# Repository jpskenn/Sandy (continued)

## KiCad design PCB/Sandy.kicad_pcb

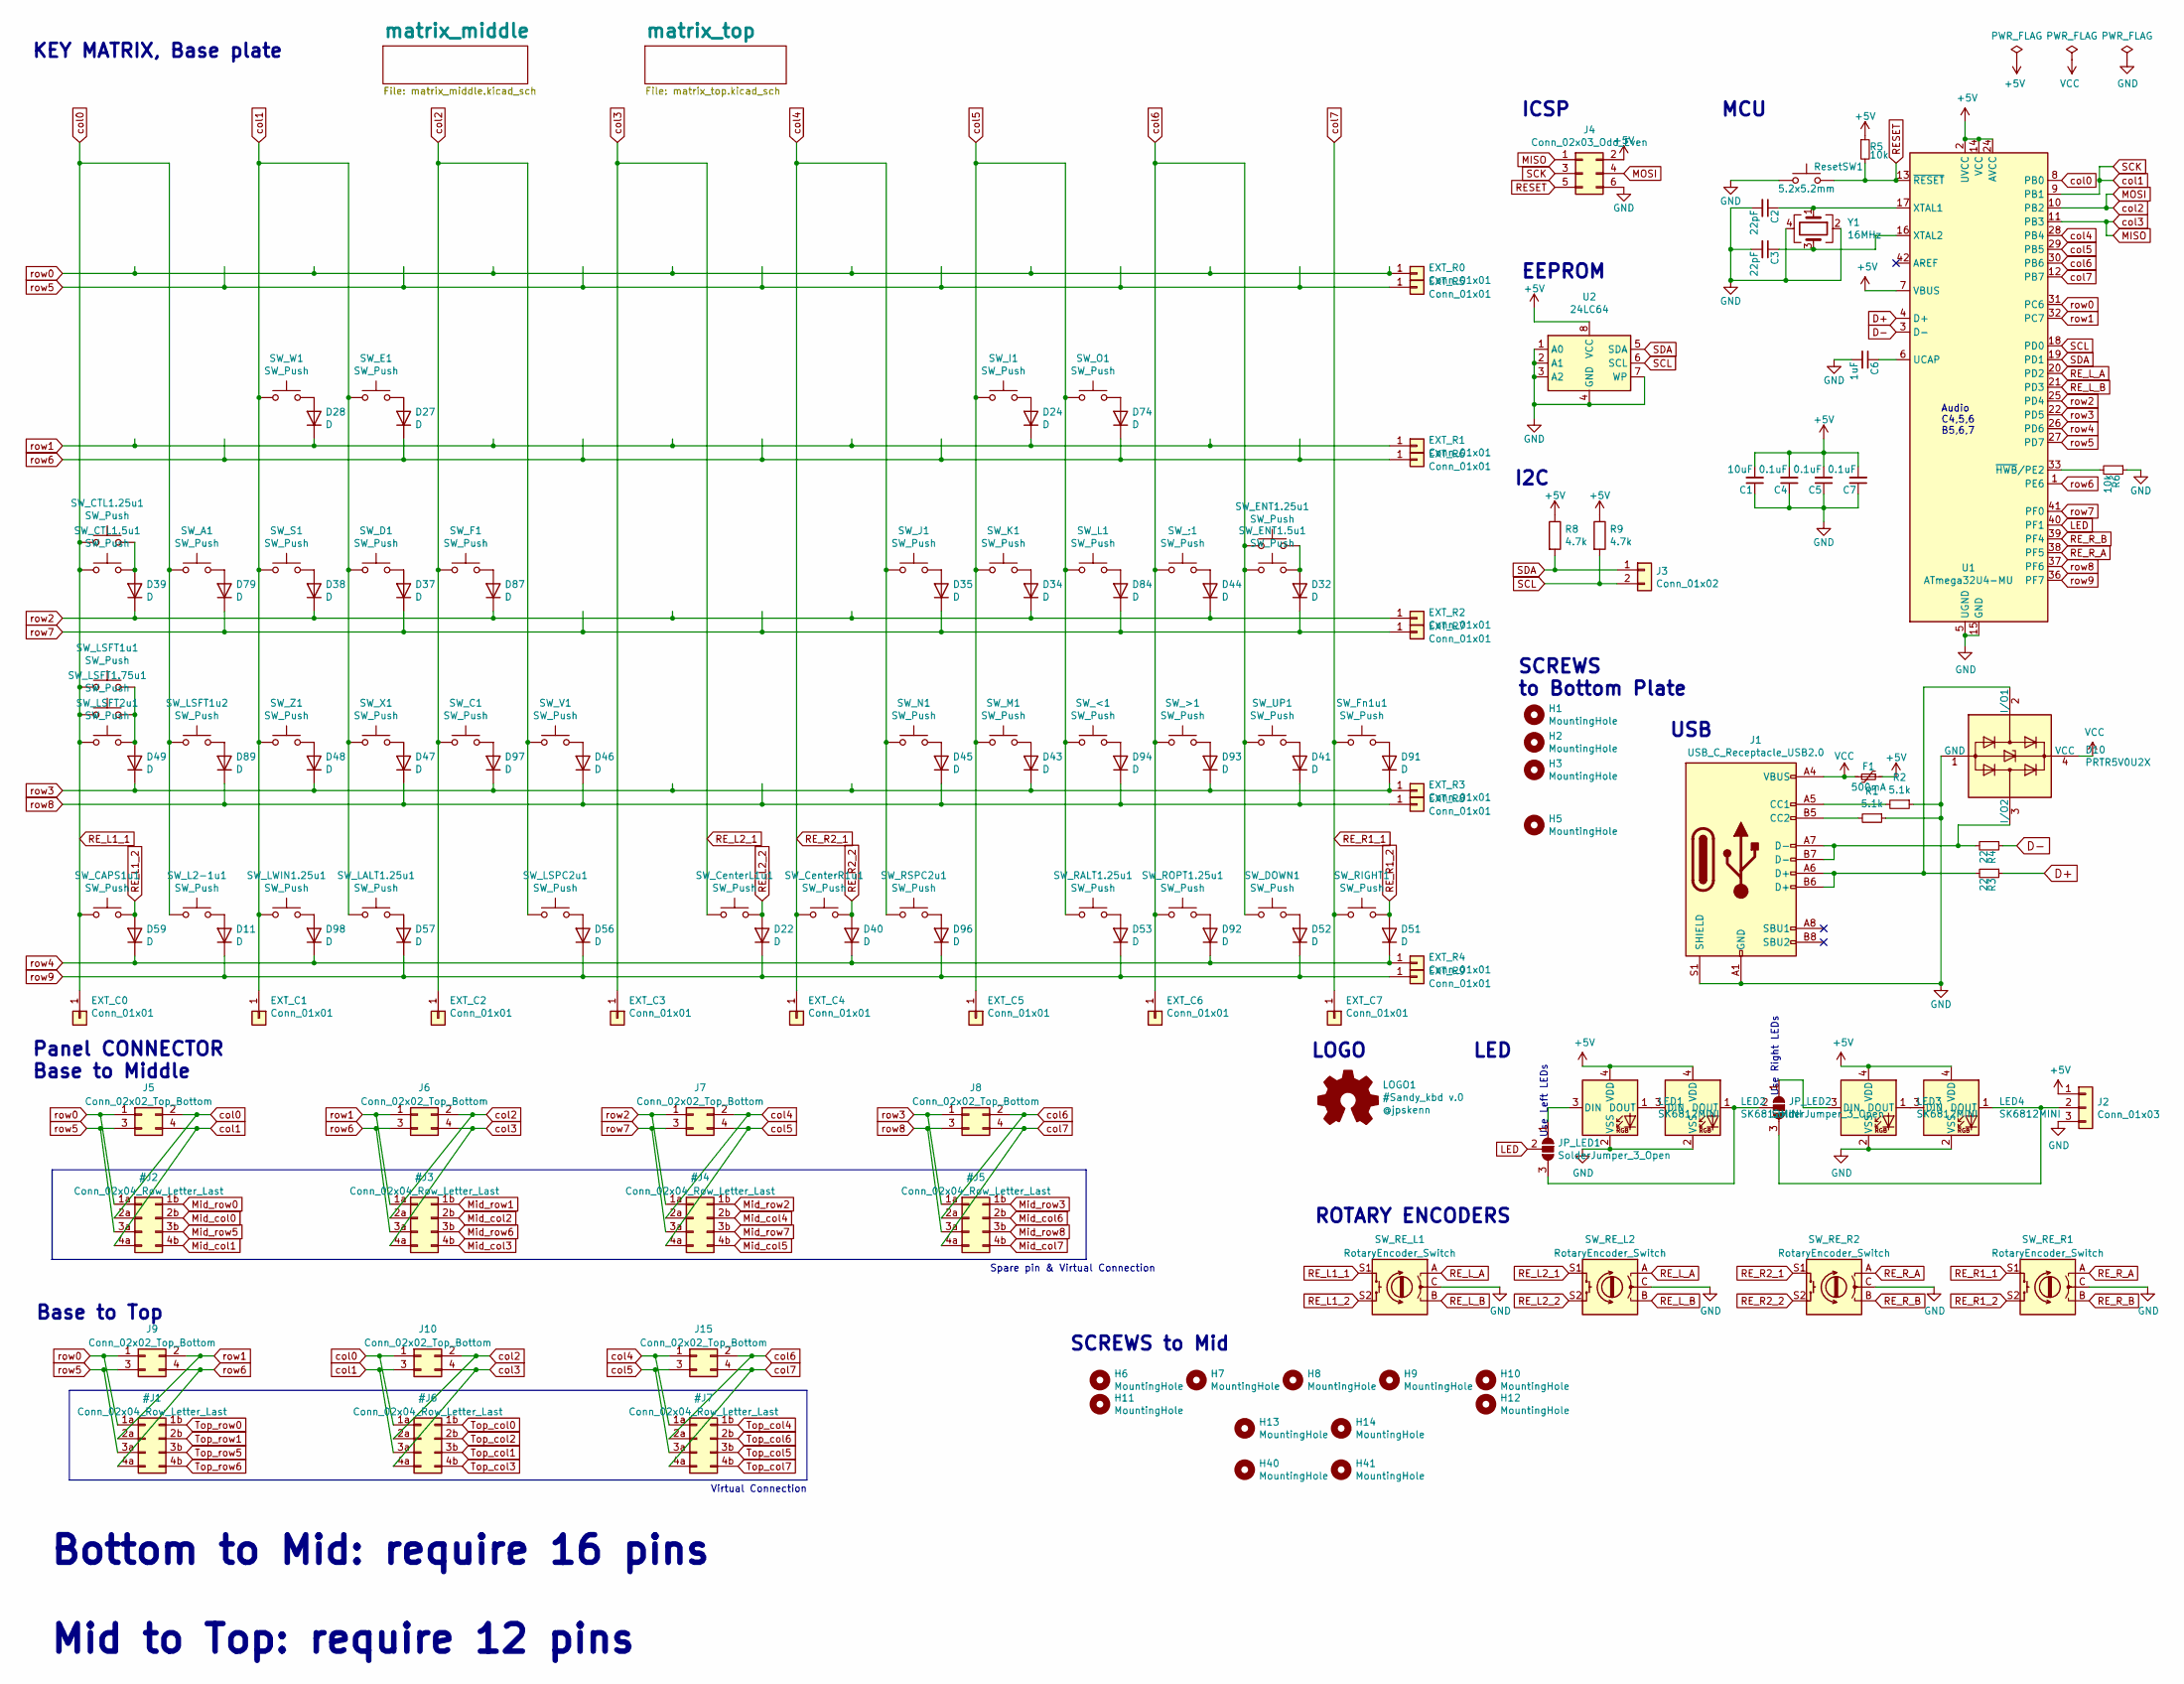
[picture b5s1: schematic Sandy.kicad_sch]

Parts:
C1: 10uF; C_0805_2012Metric_Pad1.15x1.40mm_HandSolder; LCSC C15850
C2, C3: 22pF; C_0805_2012Metric_Pad1.15x1.40mm_HandSolder; LCSC C1804
C4, C5, C7: 0.1uF; C_0805_2012Metric_Pad1.15x1.40mm_HandSolder; LCSC C49678
C6: 1uF; C_0805_2012Metric_Pad1.15x1.40mm_HandSolder; LCSC C28323
D10: PRTR5V0U2X; SOT-143; LCSC C78442
D11, D22, D24, D27, D28, D32, D34, D35, D37, D38, D39, D40, D41, D43, D44, D45, D46, D47, D48, D49, D51, D52, D53, D56, D57, D59, D74, D79, D84, D87, D89, D91, D92, D93, D94, D96, D97, D98: D; D_SOD-123; LCSC C81598
EXT_C0, EXT_C1, EXT_C2, EXT_C3, EXT_C4, EXT_C5, EXT_C6, EXT_C7: Conn_01x01; TestPoint_THTPad_D2.0mm_Drill1.0mm
EXT_R0, EXT_R1, EXT_R2, EXT_R3, EXT_R4, EXT_R5, EXT_R6, EXT_R7, EXT_R8, EXT_R9: Conn_01x01; TestPoint_THTPad_D2.0mm_Drill1.0mm
F1: 500mA; Fuse_1206_3216Metric_Pad1.42x1.75mm_HandSolder; LCSC C70076
H1, H2, H3, H5, H6, H7, H8, H9, H10, H11, H12, H13, H14, H40, H41: MountingHole; MountingHole_2.2mm_M2_No_Cu
J1: USB_C_Receptacle_USB2.0; USB_C_Receptacle_GCT_USB4085
J2: Conn_01x03; PinHeader_1x03_P2.54mm_Vertical
J3: Conn_01x02; PinHeader_1x02_P2.54mm_Vertical
J4: Conn_02x03_Odd_Even; PinHeader_2x03_P2.54mm_Vertical
J5, J6, J7, J8, J9, J10, J15: Conn_02x02_Top_Bottom; JST_SH_SM04B-SRSS-TB_1x04-1MP_P1.00mm_Horizontal_wCable_hou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
JP_LED1, JP_LED2: SolderJumper_3_Open; SolderJumper-3_P1.3mm_Open_Pad1.0x1.5mm_NumberLabels
LED1, LED2, LED3, LED4: SK6812MINI; LED_SK6812MINI_PLCC4_3.5x3.5mm_P1.75mm_TriangleMark
LOGO1: #Sandy_kbd v.0; Jones_logo_B_R_60x98.2
R1, R2: 5.1k; R_0805_2012Metric_Pad1.15x1.40mm_HandSolder; LCSC C27834
R3, R4: 22; R_0805_2012Metric_Pad1.15x1.40mm_HandSolder; LCSC C17561
R5, R6: 10k; R_0805_2012Metric_Pad1.15x1.40mm_HandSolder; LCSC C17414
R8, R9: 4.7k; R_0805_2012Metric_Pad1.20x1.40mm_HandSolder; LCSC C17673
ResetSW1: 5.2x5.2mm; SW_SPST_TL3342
SW_;1: SW_Push; MXOnly-1U-Hotswap-guide
SW_<1: SW_Push; MXOnly-1U-Hotswap-guide
SW_>1: SW_Push; MXOnly-1U-Hotswap-guide
SW_A1: SW_Push; MXOnly-1U-Hotswap-guide
SW_C1: SW_Push; MXOnly-1U-Hotswap-guide
SW_CAPS1u1: SW_Push; MXOnly-1U-Hotswap-on-RE-guide
SW_CTL1.5u1: SW_Push; MXOnly-1.5U-Hotswap-guide
SW_CTL1.25u1: SW_Push; MXOnly-1.25U-Hotswap-guide
SW_CenterL1u1: SW_Push; MXOnly-1U-Hotswap-on-RE-guide
SW_CenterR1u1: SW_Push; MXOnly-1U-Hotswap-on-RE-guide
SW_D1: SW_Push; MXOnly-1U-Hotswap-guide
SW_DOWN1: SW_Push; MXOnly-1U-Hotswap-guide
SW_E1: SW_Push; MXOnly-1U-Hotswap-guide
SW_ENT1.5u1: SW_Push; MXOnly-1.5U-Hotswap-guide
SW_ENT1.25u1: SW_Push; MXOnly-1.25U-Hotswap-guide
SW_F1: SW_Push; MXOnly-1U-Hotswap-guide
SW_Fn1u1: SW_Push; MXOnly-1U-Hotswap-guide
SW_I1: SW_Push; MXOnly-1U-Hotswap-guide
SW_J1: SW_Push; MXOnly-1U-Hotswap-guide
SW_K1: SW_Push; MXOnly-1U-Hotswap-guide
SW_L1, SW_L2-1u1: SW_Push; MXOnly-1U-Hotswap-guide
SW_LALT1.25u1: SW_Push; MXOnly-1.25U-Hotswap-guide
SW_LSFT1.75u1: SW_Push; MXOnly-1.75U-NoLED
SW_LSFT1u1, SW_LSFT1u2: SW_Push; MXOnly-1U-Hotswap-guide
SW_LSFT2u1: SW_Push; MXOnly-2U-Hotswap-guide2
SW_LSPC2u1: SW_Push; MXOnly-2U-Hotswap-ReversedStabilizers-guide2
SW_LWIN1.25u1: SW_Push; MXOnly-1.25U-Hotswap-guide
SW_M1: SW_Push; MXOnly-1U-Hotswap-guide
SW_N1: SW_Push; MXOnly-1U-Hotswap-guide
SW_O1: SW_Push; MXOnly-1U-Hotswap-guide
SW_RALT1.25u1: SW_Push; MXOnly-1.25U-Hotswap-guide
SW_RE_L1, SW_RE_L2: RotaryEncoder_Switch; RotaryEncoder_Alps_EC11K-Switch_Vertical_H20mm_NPTH_MP
SW_RE_R1, SW_RE_R2: RotaryEncoder_Switch; RotaryEncoder_Alps_EC11K-Switch_Vertical_H20mm_NPTH_MP
SW_RIGHT1: SW_Push; MXOnly-1U-Hotswap-on-RE-guide
SW_ROPT1.25u1: SW_Push; MXOnly-1.25U-Hotswap-guide
SW_RSPC2u1: SW_Push; MXOnly-2U-Hotswap-ReversedStabilizers-guide2
SW_S1: SW_Push; MXOnly-1U-Hotswap-guide
SW_UP1: SW_Push; MXOnly-1U-Hotswap-guide
SW_V1: SW_Push; MXOnly-1U-Hotswap-guide
SW_W1: SW_Push; MXOnly-1U-Hotswap-guide
SW_X1: SW_Push; MXOnly-1U-Hotswap-guide
SW_Z1: SW_Push; MXOnly-1U-Hotswap-guide
U1: ATmega32U4-MU; QFN-44-1EP_7x7mm_Pitch0.5mm; LCSC C45874
U2: 24LC64; SO-8_3.9x4.9mm_P1.27mm; LCSC C79988
Y1: 16MHz; Crystal_SMD_3225-4Pin_3.2x2.5mm_HandSoldering; LCSC C13738

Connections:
+5V: C1.2, C4.2, C5.2, C7.2, F1.1, J2.1, J4.2, LED1.4 (VDD), LED2.4 (VDD), LED3.4 (VDD), LED4.4 (VDD), R5.1, R8.1, R9.1, U1.2 (UVCC), U1.7 (VBUS), U1.14 (VCC), U1.24 (AVCC), U1.34 (VCC), U1.44 (AVCC), U2.8 (VCC)
D+: R3.1, U1.4 (D+)
D-: R4.1, U1.3 (D-)
GND: C1.1, C2.2, C3.2, C4.1, C5.1, C6.2, C7.1, D10.1 (GND), J1.A1 (GND), J1.A12 (GND), J1.B1 (GND), J1.B12 (GND), J1.S1 (SHIELD), J2.3, J4.6, LED1.2 (VSS), LED2.2 (VSS), LED3.2 (VSS), LED4.2 (VSS), R1.1, R2.1, R6.1, ResetSW1.1, SW_RE_L1.C, SW_RE_L2.C, SW_RE_R1.C, SW_RE_R2.C, U1.5 (UGND), U1.15 (GND), U1.23 (GND), U1.35 (GND), U1.43 (GND), U1.45 (GND), U2.1 (A0), U2.2 (A1), U2.3 (A2), U2.4 (GND), U2.7 (WP), Y1.2, Y1.4
LED: JP_LED1.2 (C), U1.40 (PF1)
unnamed: C2.1, U1.17 (XTAL1), Y1.1
unnamed: C3.1, U1.16 (XTAL2), Y1.3
unnamed: C6.1, U1.6 (UCAP)
unnamed: D10.2 (I/O1), J1.A6 (D+), J1.B6 (D+), R3.2
unnamed: D10.3 (I/O2), J1.A7 (D-), J1.B7 (D-), R4.2
unnamed: D11.2 (A), SW_L2-1u1.2
unnamed: D24.2 (A), SW_I1.2
unnamed: D27.2 (A), SW_E1.2
unnamed: D28.2 (A), SW_W1.2
unnamed: D32.2 (A), SW_ENT1.5u1.2, SW_ENT1.25u1.2
unnamed: D34.2 (A), SW_K1.2
unnamed: D35.2 (A), SW_J1.2
unnamed: D37.2 (A), SW_D1.2
unnamed: D38.2 (A), SW_S1.2
unnamed: D39.2 (A), SW_CTL1.5u1.2, SW_CTL1.25u1.2
unnamed: D41.2 (A), SW_UP1.2
unnamed: D43.2 (A), SW_M1.2
unnamed: D44.2 (A), SW_;1.2
unnamed: D45.2 (A), SW_N1.2
unnamed: D46.2 (A), SW_V1.2
unnamed: D47.2 (A), SW_X1.2
unnamed: D48.2 (A), SW_Z1.2
unnamed: D49.2 (A), SW_LSFT1.75u1.2, SW_LSFT1u1.2, SW_LSFT2u1.2
unnamed: D52.2 (A), SW_DOWN1.2
unnamed: D53.2 (A), SW_RALT1.25u1.2
unnamed: D56.2 (A), SW_LSPC2u1.2
unnamed: D57.2 (A), SW_LALT1.25u1.2
unnamed: D74.2 (A), SW_O1.2
unnamed: D79.2 (A), SW_A1.2
unnamed: D84.2 (A), SW_L1.2
unnamed: D87.2 (A), SW_F1.2
unnamed: D89.2 (A), SW_LSFT1u2.2
unnamed: D91.2 (A), SW_Fn1u1.2
unnamed: D92.2 (A), SW_ROPT1.25u1.2
unnamed: D93.2 (A), SW_>1.2
unnamed: D94.2 (A), SW_<1.2
unnamed: D96.2 (A), SW_RSPC2u1.2
unnamed: D97.2 (A), SW_C1.2
unnamed: D98.2 (A), SW_LWIN1.25u1.2
unnamed: J1.A5 (CC1), R2.2
unnamed: J1.B5 (CC2), R1.2
unnamed: J2.2, JP_LED2.3 (B), LED4.1 (DOUT)
unnamed: JP_LED1.1 (A), LED1.3 (DIN)
unnamed: JP_LED1.3 (B), JP_LED2.2 (C), LED2.1 (DOUT)
unnamed: JP_LED2.1 (A), LED3.3 (DIN)
unnamed: LED1.1 (DOUT), LED2.3 (DIN)
unnamed: LED3.1 (DOUT), LED4.3 (DIN)
unnamed: R6.2, U1.33 (~HWB/PE2)
RESET: J4.5, R5.2, ResetSW1.2, U1.13 (~RESET)
RE_L1_2: D59.2 (A), SW_CAPS1u1.2, SW_RE_L1.S2
RE_L2_2: D22.2 (A), SW_CenterL1u1.2, SW_RE_L2.S2
RE_L_A: SW_RE_L1.A, SW_RE_L2.A, U1.20 (PD2)
RE_L_B: SW_RE_L1.B, SW_RE_L2.B, U1.21 (PD3)
RE_R1_2: D51.2 (A), SW_RE_R1.S2, SW_RIGHT1.2
RE_R2_2: D40.2 (A), SW_CenterR1u1.2, SW_RE_R2.S2
RE_R_A: SW_RE_R1.A, SW_RE_R2.A, U1.38 (PF5)
RE_R_B: SW_RE_R1.B, SW_RE_R2.B, U1.39 (PF4)
SCL: J3.2, R9.2, U1.18 (PD0), U2.6 (SCL)
SDA: J3.1, R8.2, U1.19 (PD1), U2.5 (SDA)
VCC: D10.4 (VCC), F1.2, J1.A4 (VBUS), J1.A9 (VBUS), J1.B4 (VBUS), J1.B9 (VBUS)
row4: D40.1 (K), D51.1 (K), D59.1 (K), D92.1 (K), D98.1 (K), EXT_R4.1, U1.26 (PD6)
row9: D11.1 (K), D22.1 (K), D52.1 (K), D53.1 (K), D56.1 (K), D57.1 (K), D96.1 (K), EXT_R9.1, U1.36 (PF7)

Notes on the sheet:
Use Right LEDs
SCREWS to Mid
SCREWS to Bottom Plate
ICSP
Virtual Connection
Spare pin & Virtual Connection
Bottom to Mid: require 16 pins Mid to Top: require 12 pins
Panel CONNECTOR Base to Middle
Audio C4,5,6 B5,6,7
MCU
USB
LOGO
EEPROM
Base to Top
Use Left LEDs
LED
KEY MATRIX, Base plate
I2C
ROTARY ENCODERS

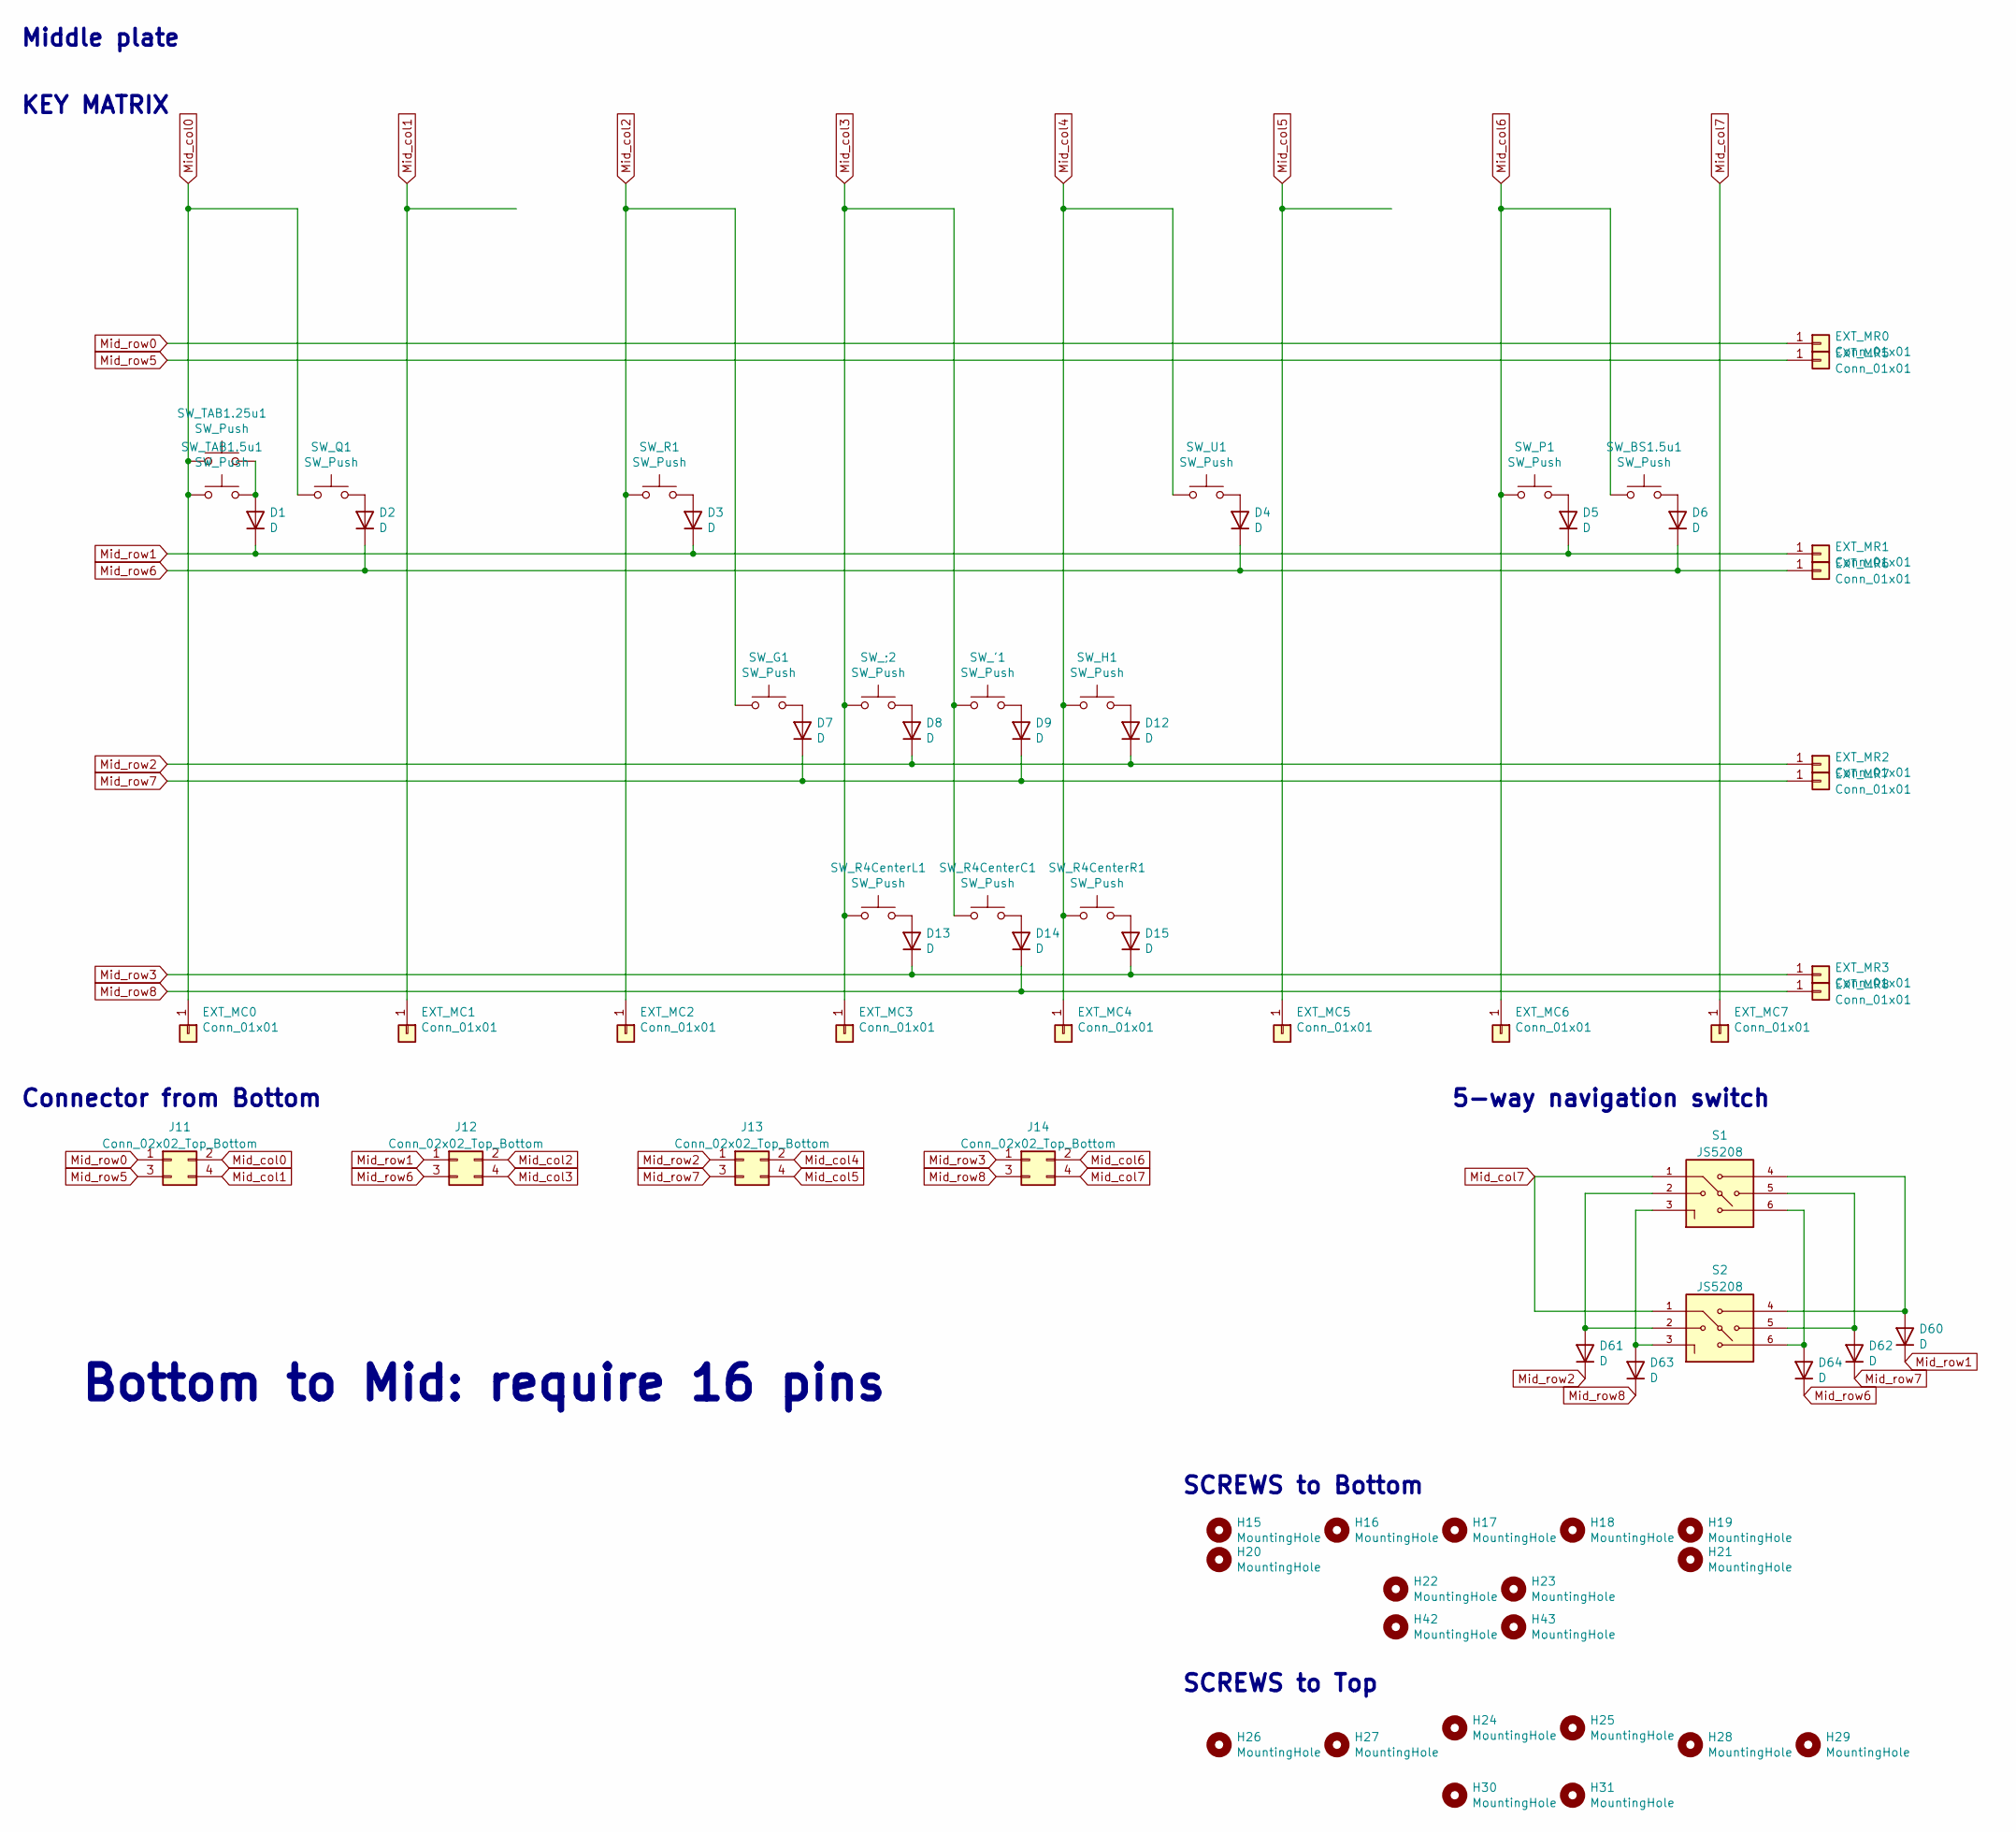
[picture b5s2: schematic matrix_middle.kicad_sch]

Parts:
D1, D2, D3, D4, D5, D6, D7, D8, D9, D12, D13, D14, D15, D60, D61, D62, D63, D64: D; D_SOD-123; LCSC C81598
EXT_MC0, EXT_MC1, EXT_MC2, EXT_MC3, EXT_MC4, EXT_MC5, EXT_MC6, EXT_MC7: Conn_01x01; TestPoint_THTPad_D2.0mm_Drill1.0mm
EXT_MR0, EXT_MR1, EXT_MR2, EXT_MR3, EXT_MR5, EXT_MR6, EXT_MR7, EXT_MR8: Conn_01x01; TestPoint_THTPad_D2.0mm_Drill1.0mm
H15, H16, H17, H18, H19, H20, H21, H22, H23, H24, H25, H26, H27, H28, H29, H30, H31, H42, H43: MountingHole; MountingHole_2.2mm_M2_No_Cu
J11, J12, J13, J14: Conn_02x02_Top_Bottom; JST_SH_SM04B-SRSS-TB_1x04-1MP_P1.00mm_Horizontal_wCable_hou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
S1, S2: JS5208; SW_JS5208_add_MP_hole; PARTREV D
SW_'1: SW_Push; MXOnly-1U-Hotswap-guide
SW_;2: SW_Push; MXOnly-1U-Hotswap-guide
SW_BS1.5u1: SW_Push; MXOnly-1.5U-Hotswap-guide
SW_G1: SW_Push; MXOnly-1U-Hotswap-guide
SW_H1: SW_Push; MXOnly-1U-Hotswap-guide
SW_P1: SW_Push; MXOnly-1U-Hotswap-guide
SW_Q1: SW_Push; MXOnly-1U-Hotswap-guide
SW_R1, SW_R4CenterC1, SW_R4CenterL1, SW_R4CenterR1: SW_Push; MXOnly-1U-Hotswap-guide
SW_TAB1.5u1: SW_Push; MXOnly-1.5U-Hotswap-guide
SW_TAB1.25u1: SW_Push; MXOnly-1.25U-NoLED
SW_U1: SW_Push; MXOnly-1U-Hotswap-guide

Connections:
Mid_col0: EXT_MC0.1, J11.2, SW_Q1.1, SW_TAB1.5u1.1, SW_TAB1.25u1.1
Mid_col1: EXT_MC1.1, J11.4
Mid_col2: EXT_MC2.1, J12.2, SW_G1.1, SW_R1.1
Mid_col3: EXT_MC3.1, J12.4, SW_'1.1, SW_;2.1, SW_R4CenterC1.1, SW_R4CenterL1.1
Mid_col4: EXT_MC4.1, J13.2, SW_H1.1, SW_R4CenterR1.1, SW_U1.1
Mid_col5: EXT_MC5.1, J13.4
Mid_col6: EXT_MC6.1, J14.2, SW_BS1.5u1.1, SW_P1.1
Mid_col7: EXT_MC7.1, J14.4, S1.1, S2.1
Mid_row0: EXT_MR0.1, J11.1
Mid_row1: D1.1 (K), D3.1 (K), D5.1 (K), D60.1 (K), EXT_MR1.1, J12.1
Mid_row2: D8.1 (K), D12.1 (K), D61.1 (K), EXT_MR2.1, J13.1
Mid_row3: D13.1 (K), D15.1 (K), EXT_MR3.1, J14.1
Mid_row5: EXT_MR5.1, J11.3
Mid_row6: D2.1 (K), D4.1 (K), D6.1 (K), D64.1 (K), EXT_MR6.1, J12.3
Mid_row7: D7.1 (K), D9.1 (K), D62.1 (K), EXT_MR7.1, J13.3
Mid_row8: D14.1 (K), D63.1 (K), EXT_MR8.1, J14.3
unnamed: D1.2 (A), SW_TAB1.5u1.2, SW_TAB1.25u1.2
unnamed: D2.2 (A), SW_Q1.2
unnamed: D3.2 (A), SW_R1.2
unnamed: D4.2 (A), SW_U1.2
unnamed: D5.2 (A), SW_P1.2
unnamed: D6.2 (A), SW_BS1.5u1.2
unnamed: D7.2 (A), SW_G1.2
unnamed: D8.2 (A), SW_;2.2
unnamed: D9.2 (A), SW_'1.2
unnamed: D12.2 (A), SW_H1.2
unnamed: D13.2 (A), SW_R4CenterL1.2
unnamed: D14.2 (A), SW_R4CenterC1.2
unnamed: D15.2 (A), SW_R4CenterR1.2
unnamed: D60.2 (A), S1.4, S2.4
unnamed: D61.2 (A), S1.2, S2.2
unnamed: D62.2 (A), S1.5, S2.5
unnamed: D63.2 (A), S1.3, S2.3
unnamed: D64.2 (A), S1.6, S2.6

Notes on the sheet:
5-way navigation switch
SCREWS to Top
Bottom to Mid: require 16 pins
KEY MATRIX
Middle plate
Connector from Bottom
SCREWS to Bottom

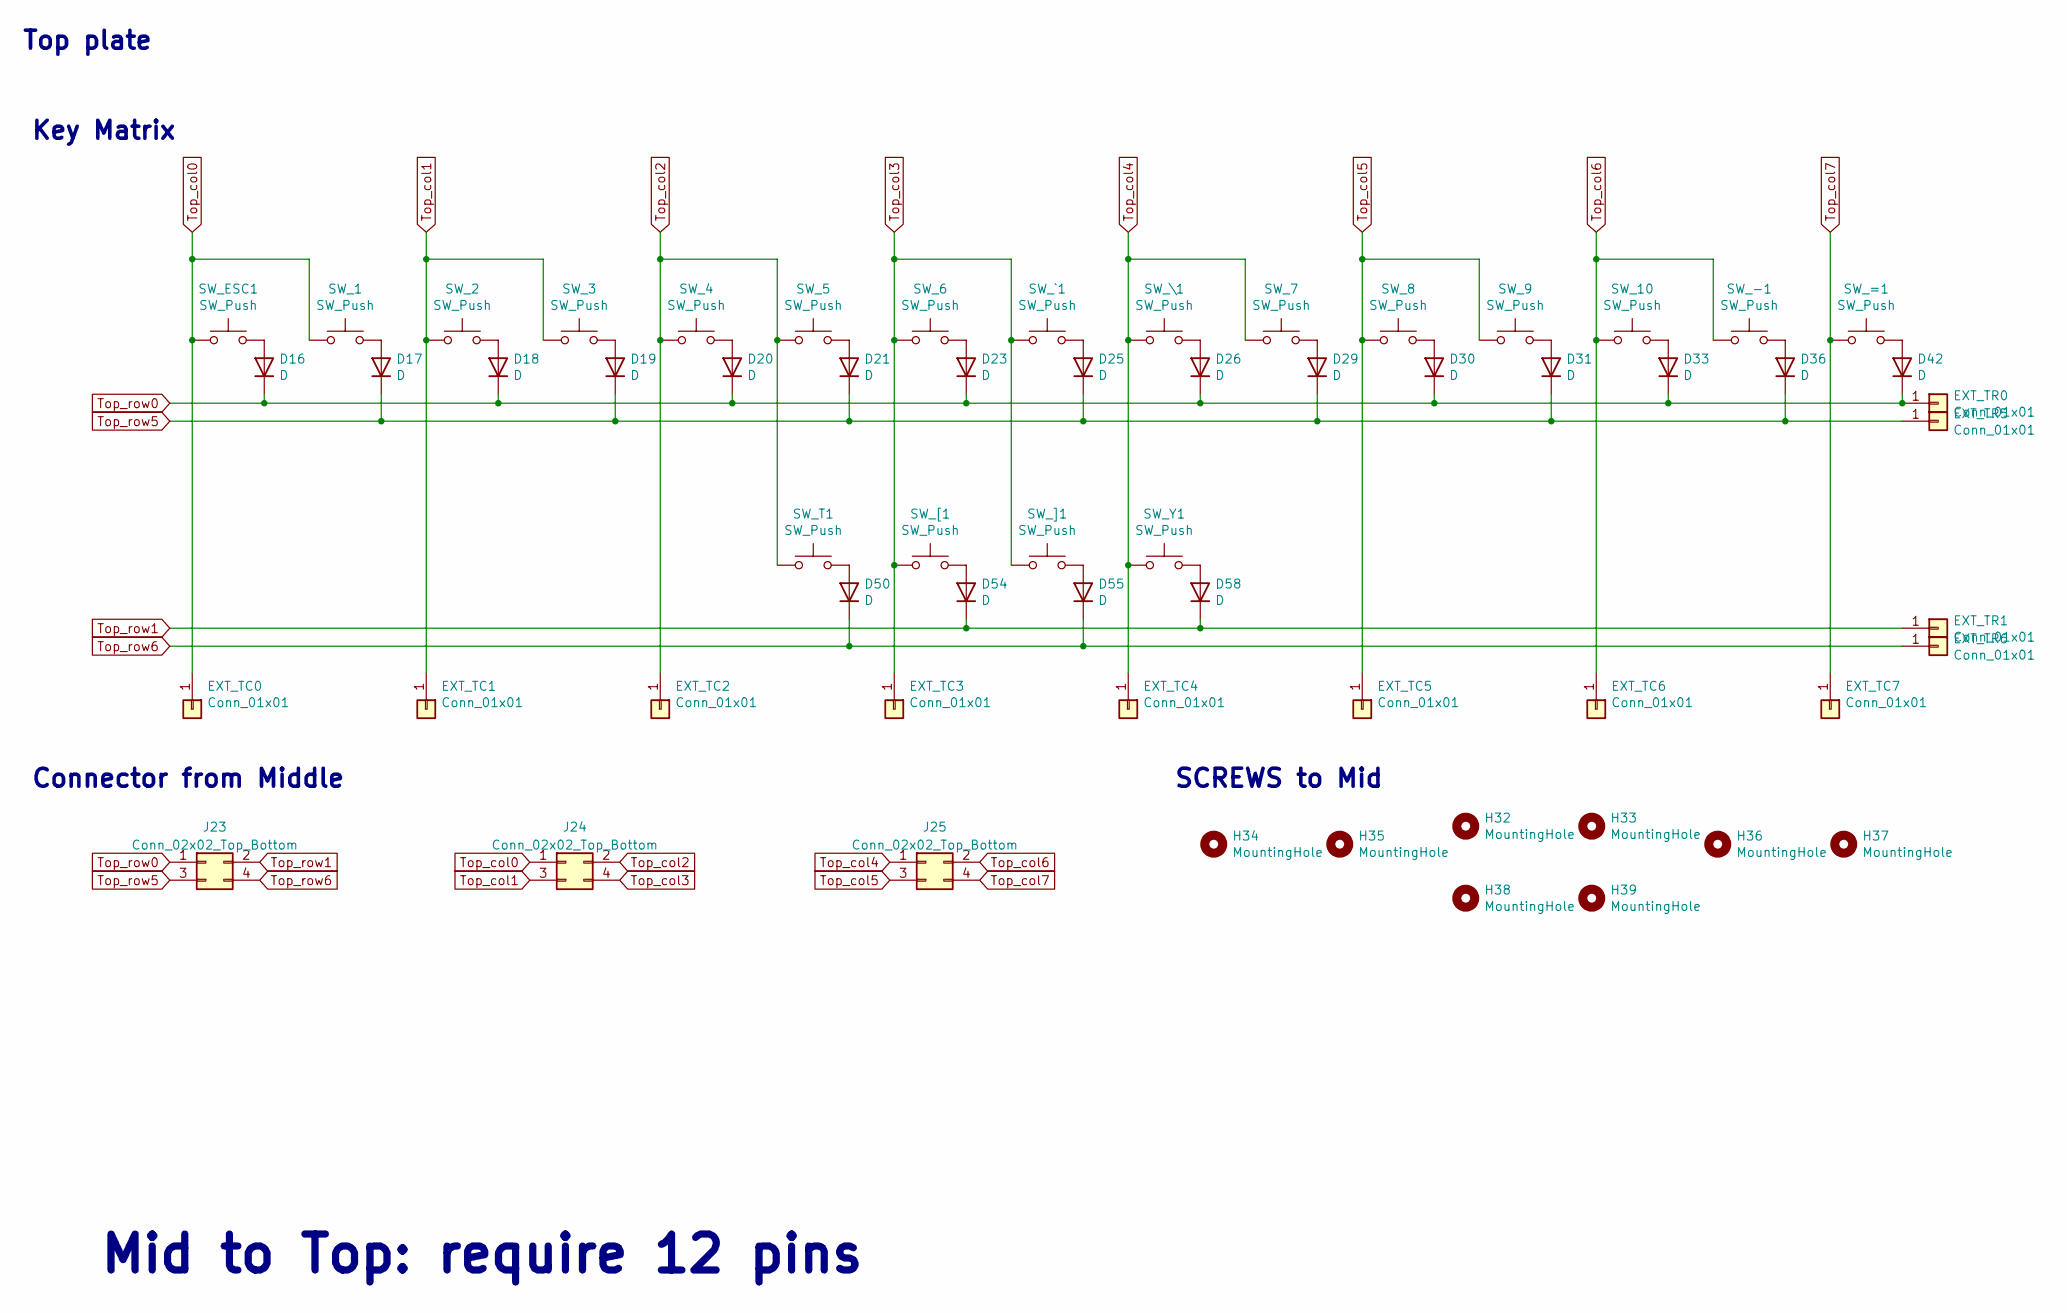
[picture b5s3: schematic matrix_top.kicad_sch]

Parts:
D16, D17, D18, D19, D20, D21, D23, D25, D26, D29, D30, D31, D33, D36, D42, D50, D54, D55, D58: D; D_SOD-123; LCSC C81598
EXT_TC0, EXT_TC1, EXT_TC2, EXT_TC3, EXT_TC4, EXT_TC5, EXT_TC6, EXT_TC7: Conn_01x01; TestPoint_THTPad_D2.0mm_Drill1.0mm
EXT_TR0, EXT_TR1, EXT_TR5, EXT_TR6: Conn_01x01; TestPoint_THTPad_D2.0mm_Drill1.0mm
H32, H33, H34, H35, H36, H37, H38, H39: MountingHole; MountingHole_2.2mm_M2_No_Cu
J23, J24, J25: Conn_02x02_Top_Bottom; JST_SH_SM04B-SRSS-TB_1x04-1MP_P1.00mm_Horizontal_wCable_hou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
SW_1, SW_2, SW_3, SW_4, SW_5, SW_6, SW_7, SW_8, SW_9, SW_10: SW_Push; MXOnly-1U-Hotswap-guide
SW_-1: SW_Push; MXOnly-1U-Hotswap-guide
SW_=1: SW_Push; MXOnly-1U-Hotswap-guide
SW_ESC1: SW_Push; MXOnly-1U-Hotswap-guide
SW_T1: SW_Push; MXOnly-1U-Hotswap-guide
SW_Y1: SW_Push; MXOnly-1U-Hotswap-guide
SW_[1: SW_Push; MXOnly-1U-Hotswap-guide
SW_\1: SW_Push; MXOnly-1U-Hotswap-guide
SW_]1: SW_Push; MXOnly-1U-Hotswap-guide
SW_`1: SW_Push; MXOnly-1U-Hotswap-guide

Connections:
unnamed: D16.2 (A), SW_ESC1.2
unnamed: D17.2 (A), SW_1.2
unnamed: D18.2 (A), SW_2.2
unnamed: D19.2 (A), SW_3.2
unnamed: D20.2 (A), SW_4.2
unnamed: D21.2 (A), SW_5.2
unnamed: D23.2 (A), SW_6.2
unnamed: D25.2 (A), SW_`1.2
unnamed: D26.2 (A), SW_\1.2
unnamed: D29.2 (A), SW_7.2
unnamed: D30.2 (A), SW_8.2
unnamed: D31.2 (A), SW_9.2
unnamed: D33.2 (A), SW_10.2
unnamed: D36.2 (A), SW_-1.2
unnamed: D42.2 (A), SW_=1.2
unnamed: D50.2 (A), SW_T1.2
unnamed: D54.2 (A), SW_[1.2
unnamed: D55.2 (A), SW_]1.2
unnamed: D58.2 (A), SW_Y1.2
Top_col0: EXT_TC0.1, J24.1, SW_1.1, SW_ESC1.1
Top_col1: EXT_TC1.1, J24.3, SW_2.1, SW_3.1
Top_col2: EXT_TC2.1, J24.2, SW_4.1, SW_5.1, SW_T1.1
Top_col3: EXT_TC3.1, J24.4, SW_6.1, SW_[1.1, SW_]1.1, SW_`1.1
Top_col4: EXT_TC4.1, J25.1, SW_7.1, SW_Y1.1, SW_\1.1
Top_col5: EXT_TC5.1, J25.3, SW_8.1, SW_9.1
Top_col6: EXT_TC6.1, J25.2, SW_10.1, SW_-1.1
Top_col7: EXT_TC7.1, J25.4, SW_=1.1
Top_row0: D16.1 (K), D18.1 (K), D20.1 (K), D23.1 (K), D26.1 (K), D30.1 (K), D33.1 (K), D42.1 (K), EXT_TR0.1, J23.1
Top_row1: D54.1 (K), D58.1 (K), EXT_TR1.1, J23.2
Top_row5: D17.1 (K), D19.1 (K), D21.1 (K), D25.1 (K), D29.1 (K), D31.1 (K), D36.1 (K), EXT_TR5.1, J23.3
Top_row6: D50.1 (K), D55.1 (K), EXT_TR6.1, J23.4

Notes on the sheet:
Key Matrix
Connector from Middle
Mid to Top: require 12 pins
SCREWS to Mid
Top plate

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
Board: 2 copper layers, 290 parts (178 on the bottom side), 148 nets, no tracks yet.

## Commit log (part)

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2023-03-28 表現変更
2023-03-28 部品リスト更新
2023-03-28 いろいろ追記
2023-03-29 だいたい手順を書き終わり
2023-03-29 写真追加、キット内容変更、説明追加
2023-03-30 試作が終わったので追記
2023-03-30 3Dに限定せず、広い範囲の話になるため、タイトル変更
2023-04-01 2台目組み立てによる経験を反映、写真追加
2023-04-01 5方向スイッチのアクチュエーションポイントについて追記
2023-04-02 基板にQRコードとURLを載せてるので不要と判断
2023-04-02 話がまとまるように整理
2023-04-02 写真追加、構成変更
2023-04-03 試作歴を開発経緯に統合。直接関係ないネタは削除。
2023-04-03 SHコネクタのパーツ番号を追加
2023-04-04 コネクタもげに対して注意喚起（3台作ってもげたことないけど）
2023-04-05 WIP, KiCad7
2023-04-07 WIP, I2Cの抵抗をネジ穴から離す
2023-04-07 WIP, issue #61
2023-04-08 Top v02（外形変更はまだ）
2023-04-08 Top 回路図のシンボル更新忘れ
2023-04-08 Mid v02（外形変更はまだ）
2023-04-08 ひととおりのソケットへの変更完了（プレートまだない）
2023-04-08 MId外形縮小
2023-04-08 各文字の位置がズレてるように見えるのを修正
2023-04-08 Topの3キーの並び順が間違えているが、互換性を保つため、修正しないコメントを追加
2023-04-08 単一レイアウトに変更
    最下行：5キー版のみ
    左シフト：2uなし、1+1のみ
2023-04-08 gitignore
2023-04-08 スイッチプレート作業開始
2023-04-08 Topプレート
2023-04-09 Mid外形縮小（基板への外形適用忘れ）
2023-04-09 Top基板にMidプレートを統合
2023-04-09 バージョン表記部分にプレートである旨を追記
2023-04-09 Base用プレート作成準備
2023-04-09 3Dモデルを指定
2023-04-09 Mid基板のディフューザーを削除
2023-04-09 Base用プレート追加
2023-04-09 不要バックアップ削除
2023-04-09 3Dチェック用エクスポートの設定変更
2023-04-09 タブそのままで実用OKと判断し、LEDディフューザータブに繋がるネジ穴を削除
2023-04-09 Top基板（Midプレート付き）からディフューザーを削除
2023-04-09 ソケットに近いSHコネクタ2個を少し後ろに下げ、ケーブルを抜き差ししやすくした
2023-04-09 base用プレートに銅箔入れ。ディフューザー調整
2023-04-09 バージョン表記調整
2023-04-09 Mid→Topのスペーサー取り付けの記述間違いを修正
2023-04-09 v02新規
2023-04-09 ダイオードの個数を記入
2023-04-09 不要シルク削除
2023-04-09 不要シルク削除、シルク調整、ベタ調整
2023-04-09 シルク調整
2023-04-10 BuildGuide_v0_2.md を更新
2023-04-10 インデント修正
2023-04-10 どのプレートを介して取り付けるかを明確に
2023-04-10 ネジ穴のシルクを、ネジを締める側にシルクが来るように変更
2023-04-10 ネジを締める場所をわかりやすく
2023-04-10 備考が備考であるよう、パーツの説明を修正
2023-04-10 組み立て前の確認を、組み立て作業の範囲に移動。
2023-04-10 タイトル変更
2023-04-10 説明を簡潔に
2023-04-10 更新メモ
2023-04-10 フォーマット
2023-04-10 単一レイアウトで余裕ができたため、ケース右下ネジを避ける穴を拡大
2023-04-10 ロゴにかからないように配線調整
2023-04-10 ERC, DRCチェック
2023-04-10 23個だとテープのカットがしにくいので、偶数に変更
2023-04-11 製造用ファイル仮作成
2023-04-11 ケーブル接続先の説明を追加
2023-04-11 コネクタ接続先シルクの視認性向上
2023-04-11 ボトムプレート用ネジ穴を、基板間接続ネジ穴と同様に、ネジを差し込む方向にシルクが来るように変更
2023-04-12 Base用プレートに、つけ忘れていたボトムプレート用ネジ穴を追加
2023-04-12 基板側面の処理と、スイッチプレートの準備を追記
2023-04-12 プレートの強度が心配される箇所から、マウスバイトを離す
2023-04-12 製作したリビジョンを知りたいので、バージョン表記からリビジョン番号による表記へ変更
2023-04-12 全体的に詳細化。リビジョン番号表記に変更
2023-04-13 Mid基板、BSキーだけ上下反転してるのおかしいのを修正
    Midなので、正方向にしてもソケットはケースネジ穴には干渉しない。
2023-04-13 修正：タイトル見切れ
2023-04-13 手順変更：基板MidとTopの仮止めをやめ、最初から全て止める
    Top用スイッチプレートを取り付けると、基板Topのおもて側からネジ止めできないため。
2023-04-13 修正：強度確保のため、Topプレートの枠を太くした
2023-04-13 改善：基板うら側を示すシルクを目立つように変更
2023-04-13 変更：基板の反り対策として、捨て板部分のベタをハッチングに変更
2023-04-13 不要ファイル削除
2023-04-13 New：共通ボトムプレート追加
2023-04-14 調整：3Dチェック用STEPファイル出力時の基板原点合わせ
2023-04-14 修正：3D表示のソケット位置微調整 Z：-1.8mm → -1.65mm
2023-04-14 製造見積もり用ガーバー出力
2023-04-15 変更：USBコネクタをHRO TYPE-C-31-M-12に変更しSMTAに対応させる
2023-04-15 製造用ファイル出力
2023-04-16 変更：リビジョン番号表記に合わせてファイル名変更
2023-04-16 追加・変更：レイアウト画像。リンク先をDN0020へ。
2023-04-16 変更：どのリビジョンの作例かわかるように
2023-04-16 変更：レンダリングの写真へ
2023-04-16 変更：全体的に記述を追加、統一。写真を追加
2023-04-16 更新：関連ファイルを準備したので、リンク先などを変更
2023-04-16 変更：VIAの動向を終えていないため、対応の名言を避ける
2023-04-16 追記：レイアウト関連の説明、写真を追加。SemiErgoについても追記
2023-04-16 変更：DN0020に合わせる
2023-04-16 変更：サービスマニュアルのUSBを追加など
2023-04-17 変更：スイッチの表記をCherryのMXだとわかるようにした
2023-04-17 加筆・フォーマット：表現を統一、わかりやすく。基板Baseの手順を前後入れ替え
2023-04-17 変更：detailsは読みにくくなるので、作業手順では使わないことにした
2023-04-26 捨て基板を折り取るのが難しいので、ヒントを追加
2023-04-26 変更：ソケットとコネクタのパッドを離すため、コネクタを0.8mm移動
    配線調整、シルク調整、GNDベタ調整
2023-04-26 変更：コネクタのシルクがケーブルで読みにくくならない位置へ移動
2023-04-28 変更：シルクの文字方向を合わせる
2023-04-29 変更：個数間違い
2023-04-29 変更：最下行左右端それぞれ2キーの枠をなくす #86
    捨て基板への接続箇所を、弱い箇所を避けるように調整
2023-04-29 MiddleをSMTAした場合の製造費確認用ファイル出力
2023-04-29 変更：アクリル板を入れるための、パーツ移動
    ダイオード、左端スイッチの上限反転、USBコネクタ周りのパーツを移動
    Base基板の外形フットプリントで、右上ネジ穴にNPTHが残っていたのを除去。
2023-04-29 追加：使用しないソケットに”×”記号を追加
2023-04-30 WIP: 配線、VIA、ベタ調整中
2023-04-30 配線、VIA、ベタ調整
2023-04-30 配線調整
2023-04-30 追加：基板おもて側に、スイッチを逆向きに取り付けるアイコンを追加
2023-05-01 アクリルカット用デザイン案
2023-05-01 アクリルカット用作業
2023-05-01 ボトムプレートを使用するパーツ構成に変更
2023-05-01 WIP: アクリルフレーム
2023-05-01 変更：Mid基板のダイオードをBase同様に移動
2023-05-02 変更：Top基板のダイオードをBase同様に移動
2023-05-03 変更：あまり使わなそうなガイドラインを削除
2023-05-03 修正：実線の大円が片方消えていた
2023-05-03 変更：アクリルフレームが基板にかかる部分を広げるため、EEPROMを移動
    配線調整、その他パーツの位置を微調整
2023-05-03 変更：製造コスト削減のため、あまり補強の意味がない左、右、下の捨て板を削除
2023-05-04 変更：配線調整
2023-05-04 追記：キーキャップ
2023-05-05 変更：アクリルフレームを通すため、MCU関連パーツの位置を下げた。
2023-05-06 評価用に反転色を追加
2023-05-06 追記：ケーブルの処理，ボトムプレートへの取り付け
2023-05-06 変更：Base用プレートにロービジのロゴ追加
2023-05-06 変更：ロゴ位置微調整
2023-05-07 変更：アクリルフレームを通すため、ダイオードの位置を変更
2023-05-08 WIP: アンダーグローLED #98
2023-05-09 アンダーグローLED #98
2023-05-10 変更：ロータリーエンコーダの3Dモデル上下反転、未使用スイッチの3Dモデル非表示
2023-05-11 アクリルフレーム 一旦完成 #86
2023-05-11 追加：アンダーグローだけ光らせるためのLED経路ジャンパを追加
    おもて側SK6812miniと、うら側SK6812mini-Eの整合性がとれない場合の回避策を仕込む
2023-05-11 追加：おもて側LED2個にデカップリングコンデンサを追加
    JLCPCBのSMTA金額が安いので、おまじない的に追加。
    アンダーグローはオプション扱いなので実装せず。
2023-05-12 変更：QRコードやロゴが見やすいように、シルク位置を調整
2023-05-12 アクリルフレーム 微調整
2023-05-12 変更：インジケータLED2個を、SK6812MINIからMINI-Eに変更
2023-05-12 SK6812MINI-E対応
2023-05-12 遊舎工房向けカットデータ作成
2023-05-13 最下行左右端の3Dパーツ非表示
2023-05-13 更新：中央も含むことがわかるように、ロータリーエンコーダのレイアウト名を変更
2023-05-13 追加：300*100サイズのカットデータ
2023-05-13 修正：DN0020はボトムケース使用のためオプション扱い
2023-05-13 修正：使用数の間違い
2023-05-13 更新：LEDの3Dモデルの位置を微調整
2023-05-13 更新：ビルドナンバー → DN0030
2023-05-13 WIP 写真更新
2023-05-13 追加：Jonesで分割したイメージ
2023-05-14 カスタマイズガイドを追記
2023-05-14 注文用データを追加
2023-05-14 削除：フォームカットはやらない
2023-05-14 変更：モットーの文字サイズをギリギリまでおおきく
2023-05-14 削除：分解は書かなくてもわかるだろう
2023-05-14 表記をわかりやすく
2023-05-15 修正：右インジケータLEDを廃止したのに、プレートにディフューザーが残っていた
2023-05-15 説明をわかりやすく
2023-05-16 変更：ボトムプレート裏側のデザイン性向上
2023-05-16 追加：ボトムプレート裏側用のロゴ
2023-05-20 加筆、調整、写真追加
2023-05-20 3Dモデルチェック用に捨て基板なしのBase用プレートを作成
2023-05-20 写真更新
2023-05-20 組み立て完了で一区切り
2023-05-20 メモ更新
2023-05-20 加筆、写真追加
2023-05-20 ヒント、SHコネクタ関連
2023-05-21 基板側面の塗りについて追記
2023-05-21 レイアウト画像追加
2023-05-21 WIP 細フレーム部分の変形防止のため強化
2023-05-21 カタカナ名前入り版を追加
2023-05-21 商品説明ポスター用のカラーを追加
2023-05-21 ナットに”六角”不要
2023-05-21 一般的な名前に変更
2023-05-22 細かな追記
2023-05-22 伸ばすのがなんだか変に思えるので、名前から長音記号を削除
2023-05-22 開発番号について追加
2023-05-22 ビルドガイドのリンクを更新
2023-05-22 DN0030のレイアウトに変更。SemiErgoをデフォルト化
2023-05-22 レイアウト追記
2023-05-22 表記統一 Mid → Middle
2023-05-22 シンプルな表現に変更
2023-05-23 M2レンチなども使えるよう、円形から六角にパーツ型番変更
2023-05-23 修正：改行追加
2023-05-24 レイアウト関連の記述を見直し
2023-05-24 初期ファームウェアのベースレイヤ構成変更を反映
2023-05-27 組み立て時に必要と感じた説明を追記。写真追加
2023-05-27 写真に注目点を追加
2023-05-27 ジャンパの機能について記載
2023-05-27 捨て基板を折りとった後、何もしなくてもなんとかなるので、気をつけるだけにする。
2023-05-27 注意追加
2023-05-27 キャプション追加
2023-05-27 わかりやすい表現に変更。
2023-05-27 順番変更
2023-05-28 アンダーグロー追記
2023-05-28 各種ファイル配置
2023-05-28 補強を追加
2023-05-28 参考とした内容を追加
2023-05-28 表現をわかりやすく
2023-05-28 フォーマット。説明を再構成。
2023-05-28 説明を流れに沿うように
2023-05-28 補強の調整
2023-05-28 捨て基板の切り離す写真を追加
2023-05-30 LEDの点灯確認作業を追加
2023-05-30 基板側面を塗る作業を一つの手順にまとめ、作業を効率化
2023-05-30 60%プラケースに取り付け確認した結果を反映
2023-05-30 ファイル名からアスタリスクを削除
2023-05-30 説明をシンプルに
2023-05-30 プレート類の写真を追加
2023-05-30 確認結果で、基板Baseの部分だけかわることを暗示
2023-05-30 表現を完結に
2023-05-30 パーツ選定をわかりやすく
2023-05-30 ”オプション作業”の内容が”オプション部品”と混同しやすいため、名称変更
2023-05-30 LED点灯確認の写真追加
2023-05-30 リンク先を商品トップに変更
2023-05-30 基板側面の塗り関連の説明をわかりやすく
2023-05-30 ソケットの浮きに関する注意を追加
2023-05-30 取り付け済みケーブルに関する注意を追加
2023-05-30 組み立て後に〜のヒントは、作業単位でおこなう
2023-05-30 温度の表現を統一
2023-05-30 締め具合の説明をわかりやすく
2023-05-30 ソケットの説明を完結に
2023-05-30 記号をわかりやすく
2023-05-30 表記を統一
2023-05-30 LED発光部の方向を追記
2023-05-31 確認済みケース追加
2023-05-31 プラケースの加工方法を追記
2023-05-31 ケーブルの差し込み方を追記
2023-05-31 ケース取り付けの説明を追加
2023-05-31 表現を統一
2023-05-31 確認結果の答えがわかるような説明を追加
2023-05-31 表現修正
2023-05-31 ぴったりを強調
2023-06-01 仕様的な注意点を追記
2023-06-01 ファームウェアのバージョンに関して追記
2023-06-02 uncap
2023-06-03 その他部品の写真追加
2023-06-03 説明を詳しく
2023-06-03 DN0030の写真を追加
2023-06-03 アンダーグローLEDを対応に追加
2023-06-04 追加 同梱リーフレット
2023-06-06 記号修正
2023-06-06 使用しないケースネジについて追記
2023-06-06 DN0030に合わせた表現に変更
2023-06-10 サブモジュールの更新忘れ
2023-06-16 修正：基板Topのコネクタへの差し込みとダイオードの干渉を避ける #105
2023-06-16 修正：上下反転スイッチに注意喚起アイコンを追加 #107
2023-06-16 変更：Baseおもて側LED2個がMidのネジ頭と干渉しそうなので、予防策として少し移動 #110
2023-06-16 規格名修正
2023-06-16 初期ロットの作業を追記
2023-11-03 New: VIA v3 definition with rotary encoder support
2023-11-03 修正 ファームウェアのファイル名間違い
2023-11-03 QMK0.22系ファームウェア提供準備
2023-11-03 ファームウェアダウンロードリンクを指定
2023-11-03 QMK0.22系ファームウェア提供
2023-11-03 トップページにファームウェア公開のアナウンスを追加
2023-11-03 ファームウェアのソースをわかりやすく。Tagsを追加。
2023-11-03 サブモジュール更新
2023-11-26 Sandy_Plate_Bottomを複製して作業開始。基板外形変更
2024-08-26 スイッチマトリックス更新。COL7を削除してスイッチを再配置。
2024-08-26 KiCad version 8 update.
2024-08-26 WIP ネジ穴位置、スイッチ位置調整中
2024-08-27 不要なロータリーエンコーダを削除。電源シンボル更新。
2024-08-27 LEDを2個増やして4個にした
2024-08-27 リセットスイッチ位置を調整・確認中
2024-08-28 MCU置き換え
2024-08-28 Topネジ穴を仮配置
2024-08-28 Mid→Topのネジ穴を追加して配置
2024-08-29 Mid→Baseのネジ穴を追加して配置
2024-08-31 ネジ穴調整、追加
2024-08-31 スイッチの配置イメージをDN0040レイアウトに変更
2024-08-31 基板間ピン割り当て
2024-08-31 ネジ穴と接続するピンを調整中
2024-09-01 Top用プレート作成（穴はEdge.Cutじゃない方法で）
2024-09-01 ネジ位置調整
2024-09-01 Top基板のMidプレート部分変更（穴はEdge.Cutじゃない方法で）
2024-09-01 配置微調整
2024-09-01 WIP Base用プレートをEdge.Cut版を作成（ボトム用ネジ穴はまだ）
2024-09-01 Base→Bottomのネジ穴位置変更
2024-09-01 Base→Bottomのネジ穴位置変更に伴う、プレート変更。
2024-09-01 ネジ穴まわりのベタ禁止エリア調整
2024-09-01 SHコネクタ・ケーブル逃し穴の調整
2024-09-01 TopのSHコネクタ位置調整。3Dモデル作成
2024-09-02 ネジ穴メモの位置調整
2024-09-02 Topのコピーを更新
2024-09-02 TopとMidのSHコネクタ位置に合わせて、穴の位置を調整。
2024-09-02 JST SH コネクタのフットプリントにコートヤードを追加
2024-09-02 Base用プレートにネジ穴が見えないよう、ボトムプレートへのネジ位置を調整。
2024-09-02 SHコネクタで接続するピンを指定
2024-09-02 シルクがハンダマスクに切り取られる箇所をフットプリントを変更して対応
2024-09-02 パーツ番号を指定
2024-09-02 WIP シルクがハンダマスクに切り取られる箇所をフットプリントを変更して対応
2024-09-02 位置合わせガイドを削除
2024-09-02 WIP パーツ配置中
2024-09-03 WIP スピーカー追加。パーツ配置中。
2024-09-03 WIP 配線中。ハンダマスクの拡張を変更0.2→0
2024-09-03 WIP 配線中
2024-09-07 WIP だいたい配線した
2024-09-07 LED穴にパッドがかからないよう、クリアランスを調整
2024-09-07 LED窓位置調整
2024-09-07 USB配線長調整
2024-09-08 ベタにGND打ち
2024-09-08 パーツ・配線微調整。Base一旦FIX
2024-09-08 パーツ・配線微調整。Base一旦FIX（再）
2024-09-08 LED窓修正
2024-09-08 スイッチ穴をEdge.Cutsから変更
2024-09-08 WIP 配線調整
2024-09-08 パーツ・配線微調整。Mid一旦FIX
2024-09-08 GNDとMid_GNDを接続
2024-09-08 パーツ・配線微調整。Top一旦FIX（再）
2024-09-08 パーツ・配線微調整。Top Plate一旦FIX（再）
2024-09-08 GH60用の中央と右下ネジ穴を削除
2024-09-08 ネジ穴まわりのクリアランスを調整
2024-09-08 Revert "GH60用の中央と右下ネジ穴を削除"
    This reverts commit acbd52c645e442f509ad253bc26362e91d0bbea1.
2024-09-08 中央と右下ネジ穴を戻して、再調整。
2024-09-08 GNDベタ調整
2024-09-11 フットプリントをChoc V2に置き換え。まだ様子見。
2024-09-11 スイッチの3Dモデルを追加・設定
2024-09-11 WIP 配線削除中
2024-09-11 最下行左端のスイッチがグリッドからずれていたのを修正
2024-09-11 WIP 配線調整，Choc V2フットプリントテスト中
2024-09-11 WIP Choc V2のフットプリントに変更。配置考え中。
2024-09-12 WIP 4行化
2024-09-12 TopはMid用プレート兼用をやめた
2024-09-12 WIP ネジ位置等検討中
2024-09-13 Choc V2のフットプリントで固定ピンを機構穴に変更し、位置等を修正。
